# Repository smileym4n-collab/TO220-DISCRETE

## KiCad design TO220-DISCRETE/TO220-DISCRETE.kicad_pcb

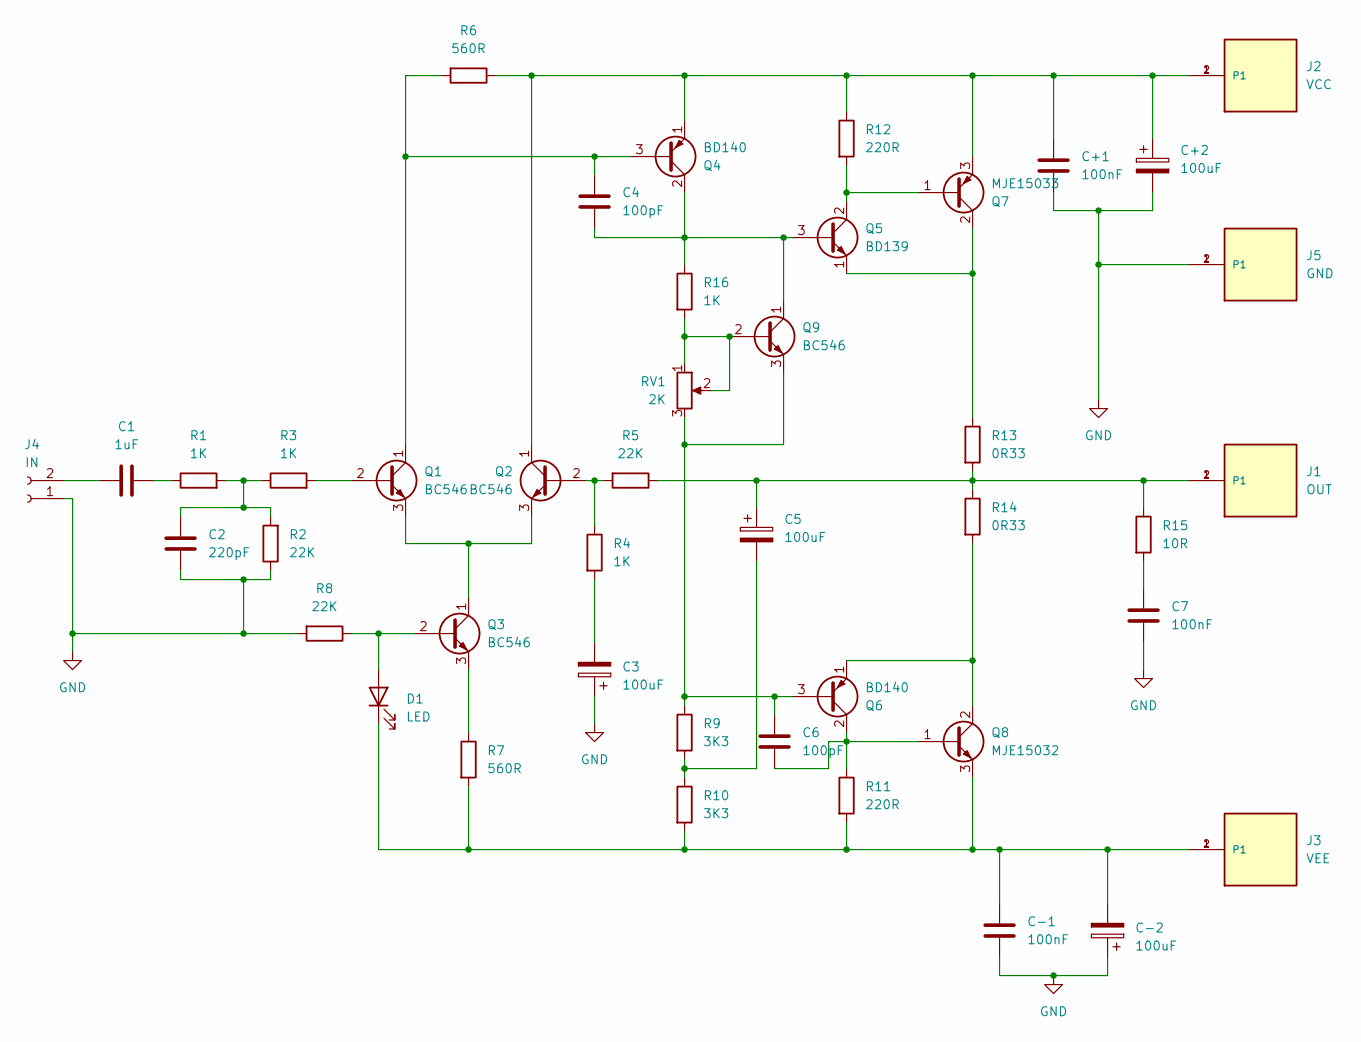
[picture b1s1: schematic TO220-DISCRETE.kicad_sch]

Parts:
C1: 1uF; C_Rect_L7.2mm_W5.5mm_P5.00mm_FKS2_FKP2_MKS2_MKP2
C2: 220pF; C_0805_2012Metric_Pad1.18x1.45mm_HandSolder
C3, C5: 100uF; CP_Radial_D8.0mm_P2.50mm
C4, C6: 100pF; C_0805_2012Metric_Pad1.18x1.45mm_HandSolder
C7: 100nF; C_1206_3216Metric_Pad1.33x1.80mm_HandSolder
C+1: 100nF; C_1206_3216Metric_Pad1.33x1.80mm_HandSolder
C+2: 100uF; CP_Radial_D8.0mm_P2.50mm
C-1: 100nF; C_1206_3216Metric_Pad1.33x1.80mm_HandSolder
C-2: 100uF; CP_Radial_D8.0mm_P2.50mm
D1: LED; LED_D5.0mm
J1: OUT; TE_62409-1; PART_DESCRIPTION CONN QC TAB 0.250 SOLDER
J2: VCC; TE_62409-1; PART_DESCRIPTION CONN QC TAB 0.250 SOLDER
J3: VEE; TE_62409-1; PART_DESCRIPTION CONN QC TAB 0.250 SOLDER
J4: IN; JST_XH_B2B-XH-A_1x02_P2.50mm_Vertical
J5: GND; TE_62409-1; PART_DESCRIPTION CONN QC TAB 0.250 SOLDER
Q1, Q2, Q3, Q9: BC546; TO-92_Inline_Wide
Q4, Q6: BD140; TO-126-3_Vertical
Q5: BD139; TO-126-3_Vertical
Q7: MJE15033; TO-220-3_Horizontal_TabDown
Q8: MJE15032; TO-220-3_Horizontal_TabDown
R1, R3, R4, R16: 1K; R_Axial_DIN0207_L6.3mm_D2.5mm_P10.16mm_Horizontal
R2, R5, R8: 22K; R_Axial_DIN0207_L6.3mm_D2.5mm_P10.16mm_Horizontal
R6, R7: 560R; R_Axial_DIN0207_L6.3mm_D2.5mm_P10.16mm_Horizontal
R9, R10: 3K3; R_Axial_DIN0207_L6.3mm_D2.5mm_P10.16mm_Horizontal
R11, R12: 220R; R_Axial_DIN0207_L6.3mm_D2.5mm_P10.16mm_Horizontal
R13, R14: 0R33; R_Axial_DIN0617_L17.0mm_D6.0mm_P25.40mm_Horizontal
R15: 10R; R_Axial_DIN0207_L6.3mm_D2.5mm_P10.16mm_Horizontal
RV1: 2K; Potentiometer_Vishay_T93YA_Vertical

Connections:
GND: C2.1, C3.1, C7.2, C+1.2, C+2.2, C-1.2, C-2.1, J4.1, J5.1, J5.2 (P1), R2.1, R8.2
unnamed: C1.2, R1.1
unnamed: C2.2, R1.2, R2.2, R3.1
unnamed: C3.2, R4.2
unnamed: C5.1, J1.1, J1.2 (P1), R5.1, R13.2, R14.1, R15.1
unnamed: C5.2, R9.2, R10.1
unnamed: C7.1, R15.2
unnamed: D1.2 (A), Q3.2 (B), R8.1
unnamed: C-1.1, C-2.2, D1.1 (K), J3.1, J3.2 (P1), Q8.3 (E), R7.2, R10.2, R11.2
unnamed: C1.1, J4.2
unnamed: Q1.2 (B), R3.2
unnamed: C4.2, Q1.1 (C), Q4.3 (B), R6.2
unnamed: Q1.3 (E), Q2.3 (E), Q3.1 (C)
unnamed: Q2.2 (B), R4.1, R5.2
unnamed: C+1.1, C+2.1, J2.1, J2.2 (P1), Q2.1 (C), Q4.1 (E), Q7.3 (E), R6.1, R12.1
unnamed: Q3.3 (E), R7.1
unnamed: C4.1, Q4.2 (C), Q5.3 (B), Q9.1 (C), R16.1
unnamed: Q5.2 (C), Q7.1 (B), R12.2
unnamed: Q5.1 (E), Q7.2 (C), R13.1
unnamed: C6.2, Q6.3 (B), Q9.3 (E), R9.1, RV1.3
unnamed: C6.1, Q6.2 (C), Q8.1 (B), R11.1
unnamed: Q6.1 (E), Q8.2 (C), R14.2
unnamed: Q9.2 (B), R16.2, RV1.1, RV1.2

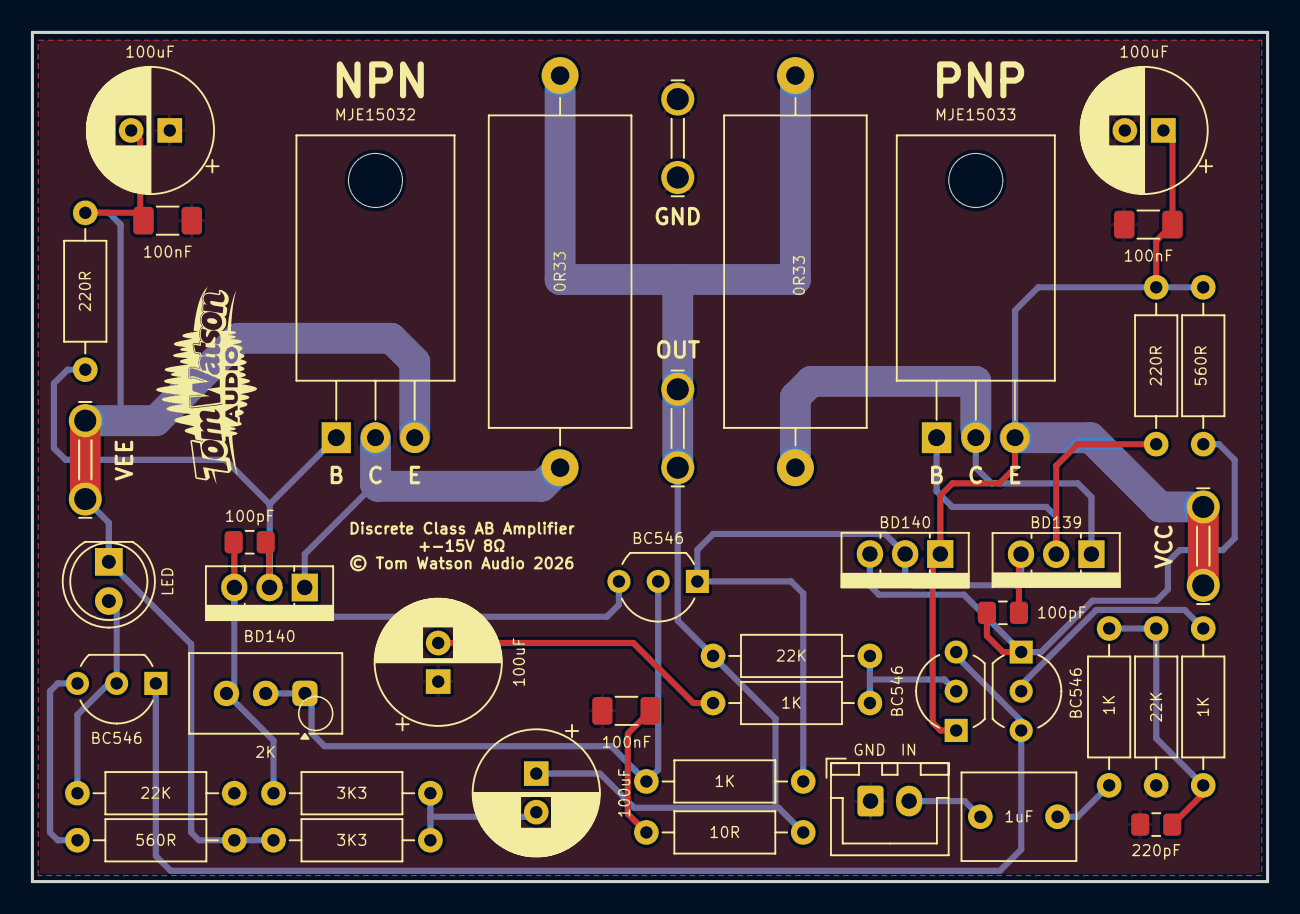
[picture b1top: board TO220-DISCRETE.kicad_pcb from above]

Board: 2 copper layers, 80.0 x 55.0 mm, 43 parts (0 on the bottom side), 23 nets.

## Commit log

2026-06-15 started
2026-06-19 board designed
2026-06-19 more work
2026-06-20 tweaks

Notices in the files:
TO220-DISCRETE/TO220-DISCRETE.kicad_pcb:
© Tom Watson Audio 2026
